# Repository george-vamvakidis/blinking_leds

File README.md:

# blinking_leds
A project in which a simple 555 IC is used in order to make two LEDs blinking in different speeds.

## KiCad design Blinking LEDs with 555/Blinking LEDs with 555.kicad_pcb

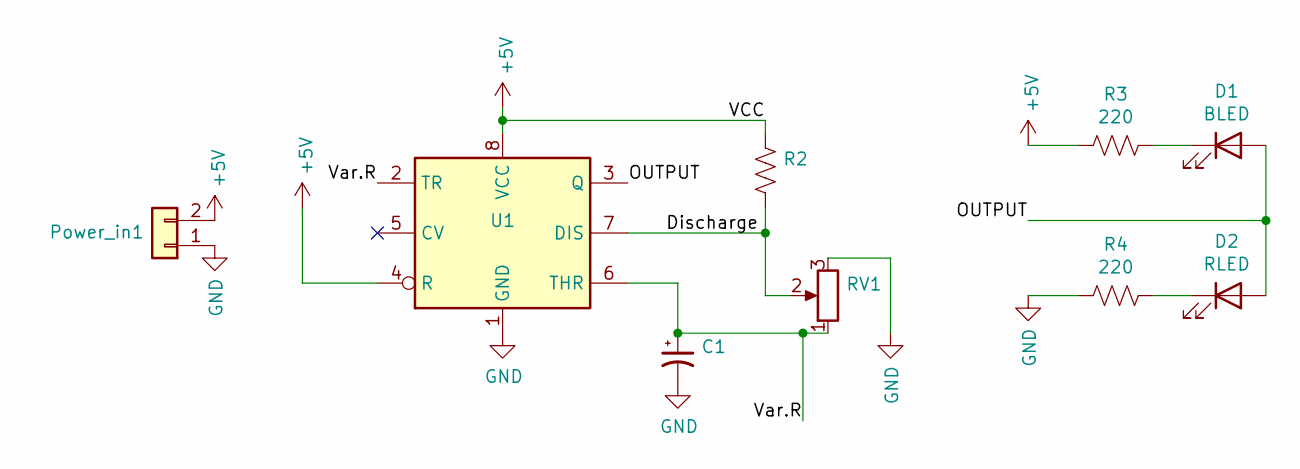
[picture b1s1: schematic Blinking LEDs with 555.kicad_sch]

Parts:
C1: 10μF; CP_Radial_Tantal_D6.0mm_P2.50mm
D1: BLED; LED_1210_3225Metric
D2: RLED; LED_1210_3225Metric
Power_in1: Conn_01x02; TerminalBlock_Altech_AK300-2_P5.00mm
R2: 1k; R_1206_3216Metric
R3, R4: 220; R_1206_3216Metric
RV1: 10k; Potentiometer_Alps_RK163_Single_Horizontal
U1: TLC555xP; DIP-8_W7.62mm

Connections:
+5V: Power_in1.2, R2.1, R3.1, U1.4 (R), U1.8 (VCC)
/Discharge: R2.2, RV1.2, U1.7 (DIS)
/OUTPUT: D1.2 (A), D2.2 (A), U1.3 (Q)
/Var.R: C1.1, RV1.1, U1.2 (TR), U1.6 (THR)
GND: C1.2, Power_in1.1, R4.1, RV1.3, U1.1 (GND)
unnamed: D1.1 (K), R3.2
unnamed: D2.1 (K), R4.2

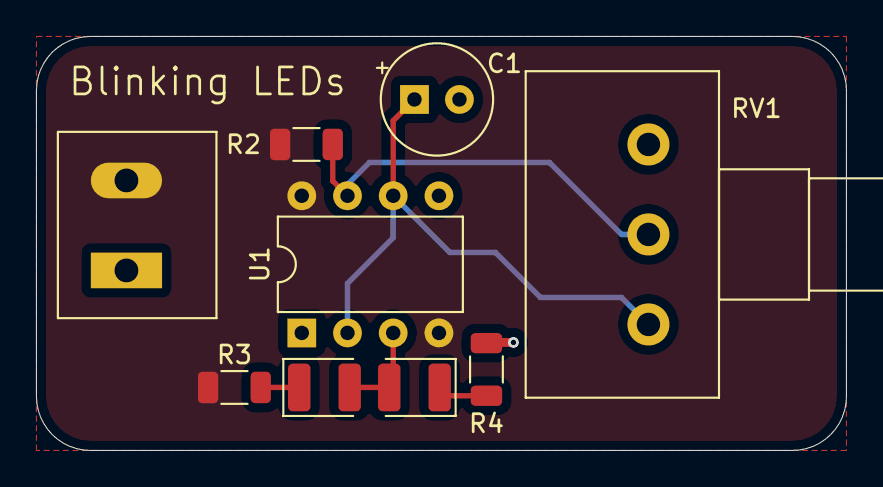
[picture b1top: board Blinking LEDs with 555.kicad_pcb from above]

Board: 2 copper layers, 45.0 x 23.0 mm, 9 parts (0 on the bottom side), 7 nets.
